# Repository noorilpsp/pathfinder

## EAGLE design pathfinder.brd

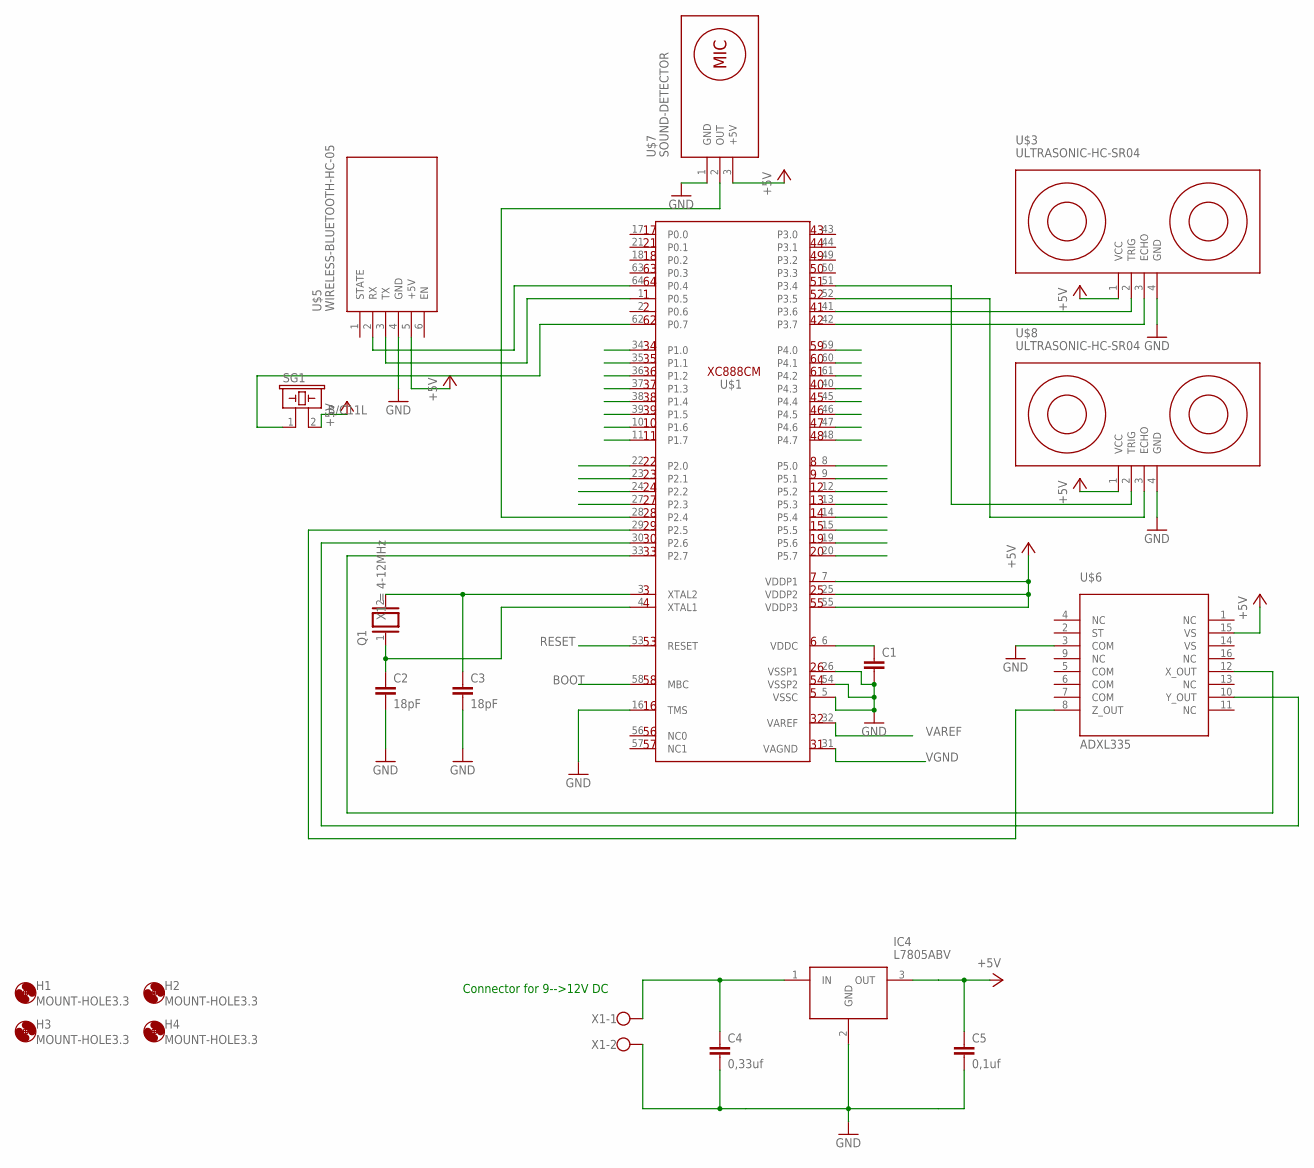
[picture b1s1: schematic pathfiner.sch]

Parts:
C1: C2,5-3; C2.5-3
C2, C3: 18pF; C2.5-3
C4: 0,33uf; C025-030X050
C5: 0,1uf; C025-030X050
H1, H2, H3, H4: MOUNT-HOLE3.3; 3,3
IC4: L7805ABV; TO270P460X1020X2008-3P
Q1: XTAL; Q
SG1: B/C11L
U$1: XC888; QFP50P1200X1200X160-64N
U$3, U$8: ULTRASONIC-HC-SR04
U$5: WIRELESS-BLUETOOTH-HC-05
U$6: ADXL335; LFCSP16
U$7: SOUND-DETECTOR
X1: W237-102

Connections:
+5V: C5.1, IC4.3 (OUT), SG1.2, U$1.7 (VDDP1), U$1.25 (VDDP2), U$1.55 (VDDP3), U$3.1 (VCC), U$5.5 (+5V), U$6.15 (VS), U$7.3 (+5V), U$8.1 (VCC)
BOOT: U$1.58 (MBC)
GND: C1.2, C2.2, C3.2, C4.2, C5.2, IC4.2 (GND), U$1.5 (VSSC), U$1.16 (TMS), U$1.26 (VSSP1), U$1.54 (VSSP2), U$3.4 (GND), U$5.4 (GND), U$6.3 (COM), U$7.1 (GND), U$8.4 (GND), X1.2
unnamed: U$1.33 (P2.7), U$6.12 (X_OUT)
unnamed: U$1.28 (P2.4), U$7.2 (OUT)
unnamed: U$1.29 (P2.5), U$6.8 (Z_OUT)
unnamed: C4.1, IC4.1 (IN), X1.1
unnamed: SG1.1, U$1.62 (P0.7)
unnamed: U$1.1 (P0.5), U$5.3 (TX)
unnamed: U$1.64 (P0.4), U$5.2 (RX)
unnamed: U$1.52 (P3.5), U$8.3 (ECHO)
unnamed: U$1.41 (P3.6), U$3.2 (TRIG)
unnamed: U$1.42 (P3.7), U$3.3 (ECHO)
unnamed: C3.1, Q1.2, U$1.3 (XTAL2)
unnamed: C2.1, Q1.1, U$1.4 (XTAL1)
unnamed: C1.1, U$1.6 (VDDC)
unnamed: U$1.51 (P3.4), U$8.2 (TRIG)
unnamed: U$1.30 (P2.6), U$6.10 (Y_OUT)
RESET: U$1.53 (RESET)
VAREF: U$1.32 (VAREF)
VGND: U$1.31 (VAGND)

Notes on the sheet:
Connector for 9-->12V DC

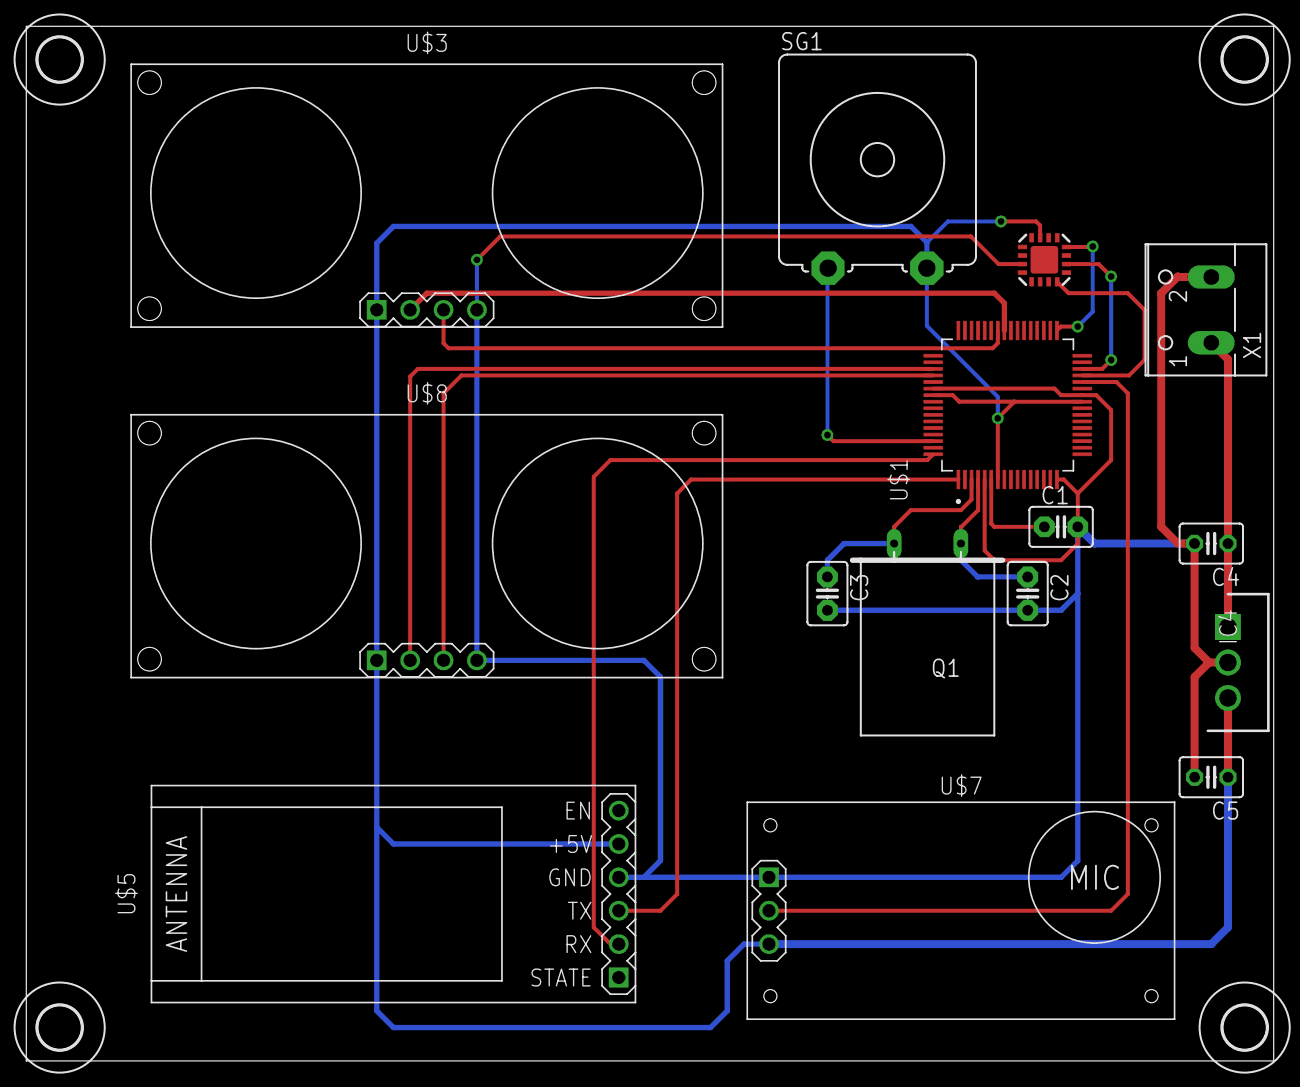
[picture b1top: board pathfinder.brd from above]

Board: 2 copper layers, 94.9 x 78.7 mm, 19 parts (0 on the bottom side), 17 nets.

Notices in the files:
parts and their libraries:
ultrasonic: Released under the Creative Commons Attribution 4.0 International License: http://creativecommons.org/licenses/by/4.0
